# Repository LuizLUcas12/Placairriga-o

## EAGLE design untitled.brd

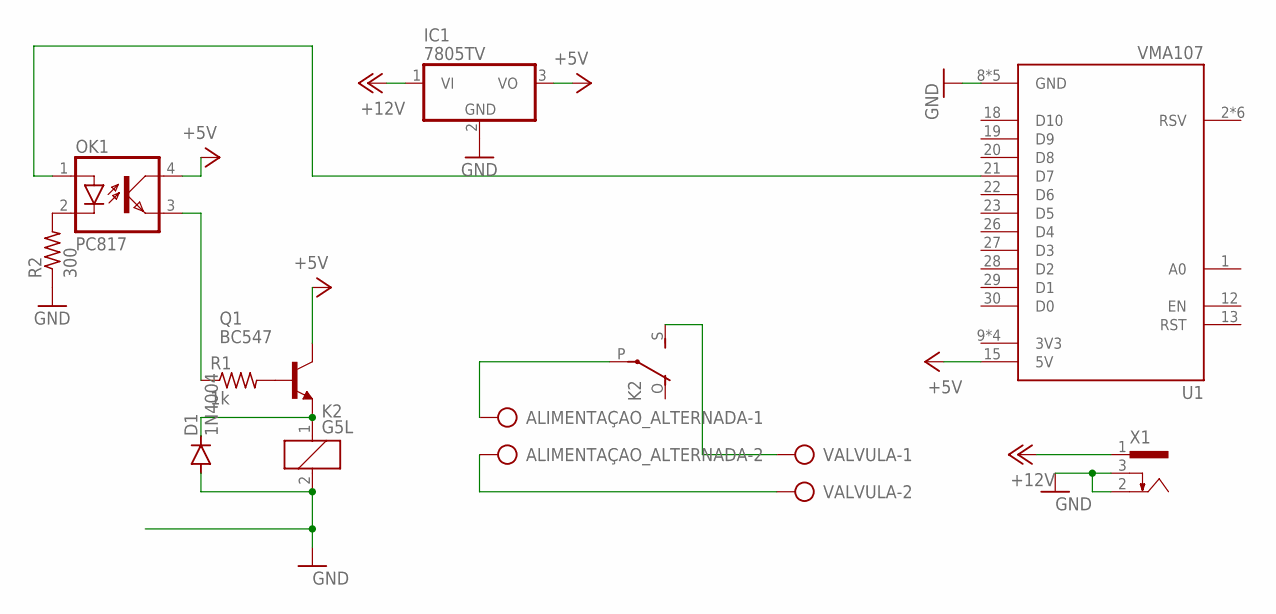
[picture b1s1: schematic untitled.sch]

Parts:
ALIMENTAÇAO_ALTERNADA: AK500/2-H
D1: 1N4004; DO41-10
IC1: 7805TV; TO220V
K2: G5L; G5LE
OK1: PC817; DIL04
Q1: BC547; TO92
R1: 1k; 0204/7
R2: 300; 0204/7
U1: VMA107; MODULE_VMA107
VALVULA: AK500/2-H
X1: 733980-62

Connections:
3V3: U1.9 (3V3), U1.11 (3V3), U1.16 (3V3), U1.25 (3V3)
+5V: IC1.3 (VO), OK1.4 (COL), Q1.3 (C), U1.15 (5V)
+12V: IC1.1 (VI), X1.1
GND: D1.A, IC1.2 (GND), K2.2, R2.1, U1.8 (GND), U1.10 (GND), U1.14 (GND), U1.17 (GND), U1.24 (GND), X1.2, X1.3
unnamed: D1.C, K2.1, Q1.1 (E)
unnamed: OK1.3 (EMIT), R1.1
unnamed: Q1.2 (B), R1.2
unnamed: OK1.2 (C), R2.2
unnamed: OK1.1 (A), U1.21 (D7)
unnamed: ALIMENTAÇAO_ALTERNADA.1, K2.P
unnamed: K2.S, VALVULA.1
unnamed: ALIMENTAÇAO_ALTERNADA.2, VALVULA.2

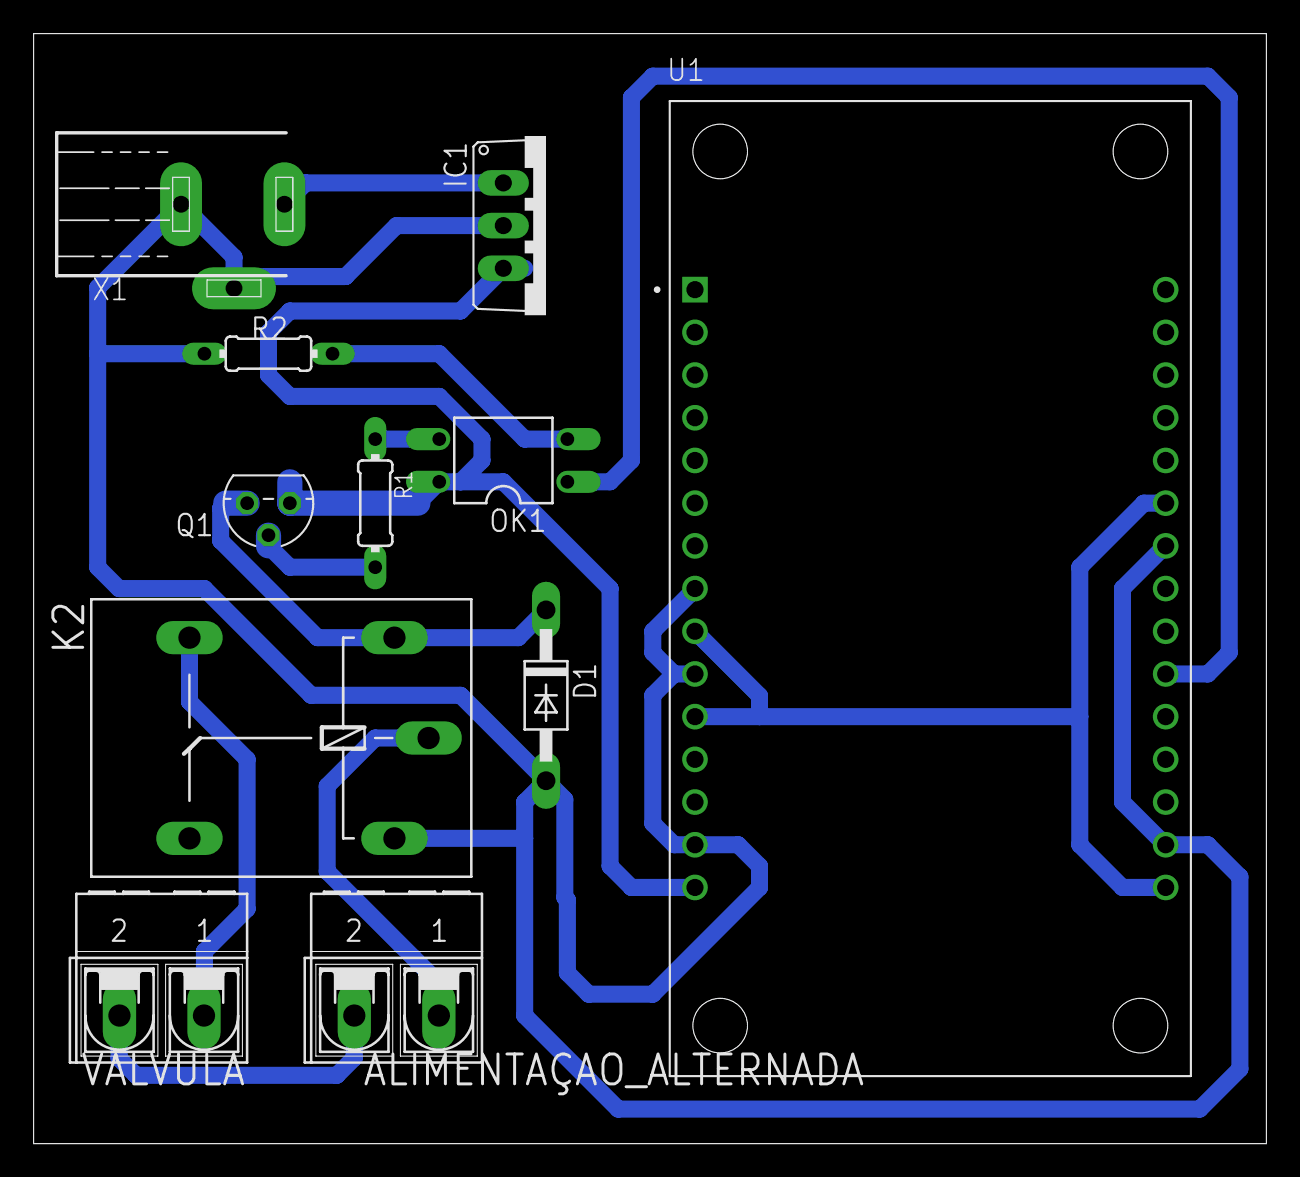
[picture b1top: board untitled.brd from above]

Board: 2 copper layers, 73.3 x 66.0 mm, 11 parts (0 on the bottom side), 12 nets.

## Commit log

2024-07-27 placairrig
